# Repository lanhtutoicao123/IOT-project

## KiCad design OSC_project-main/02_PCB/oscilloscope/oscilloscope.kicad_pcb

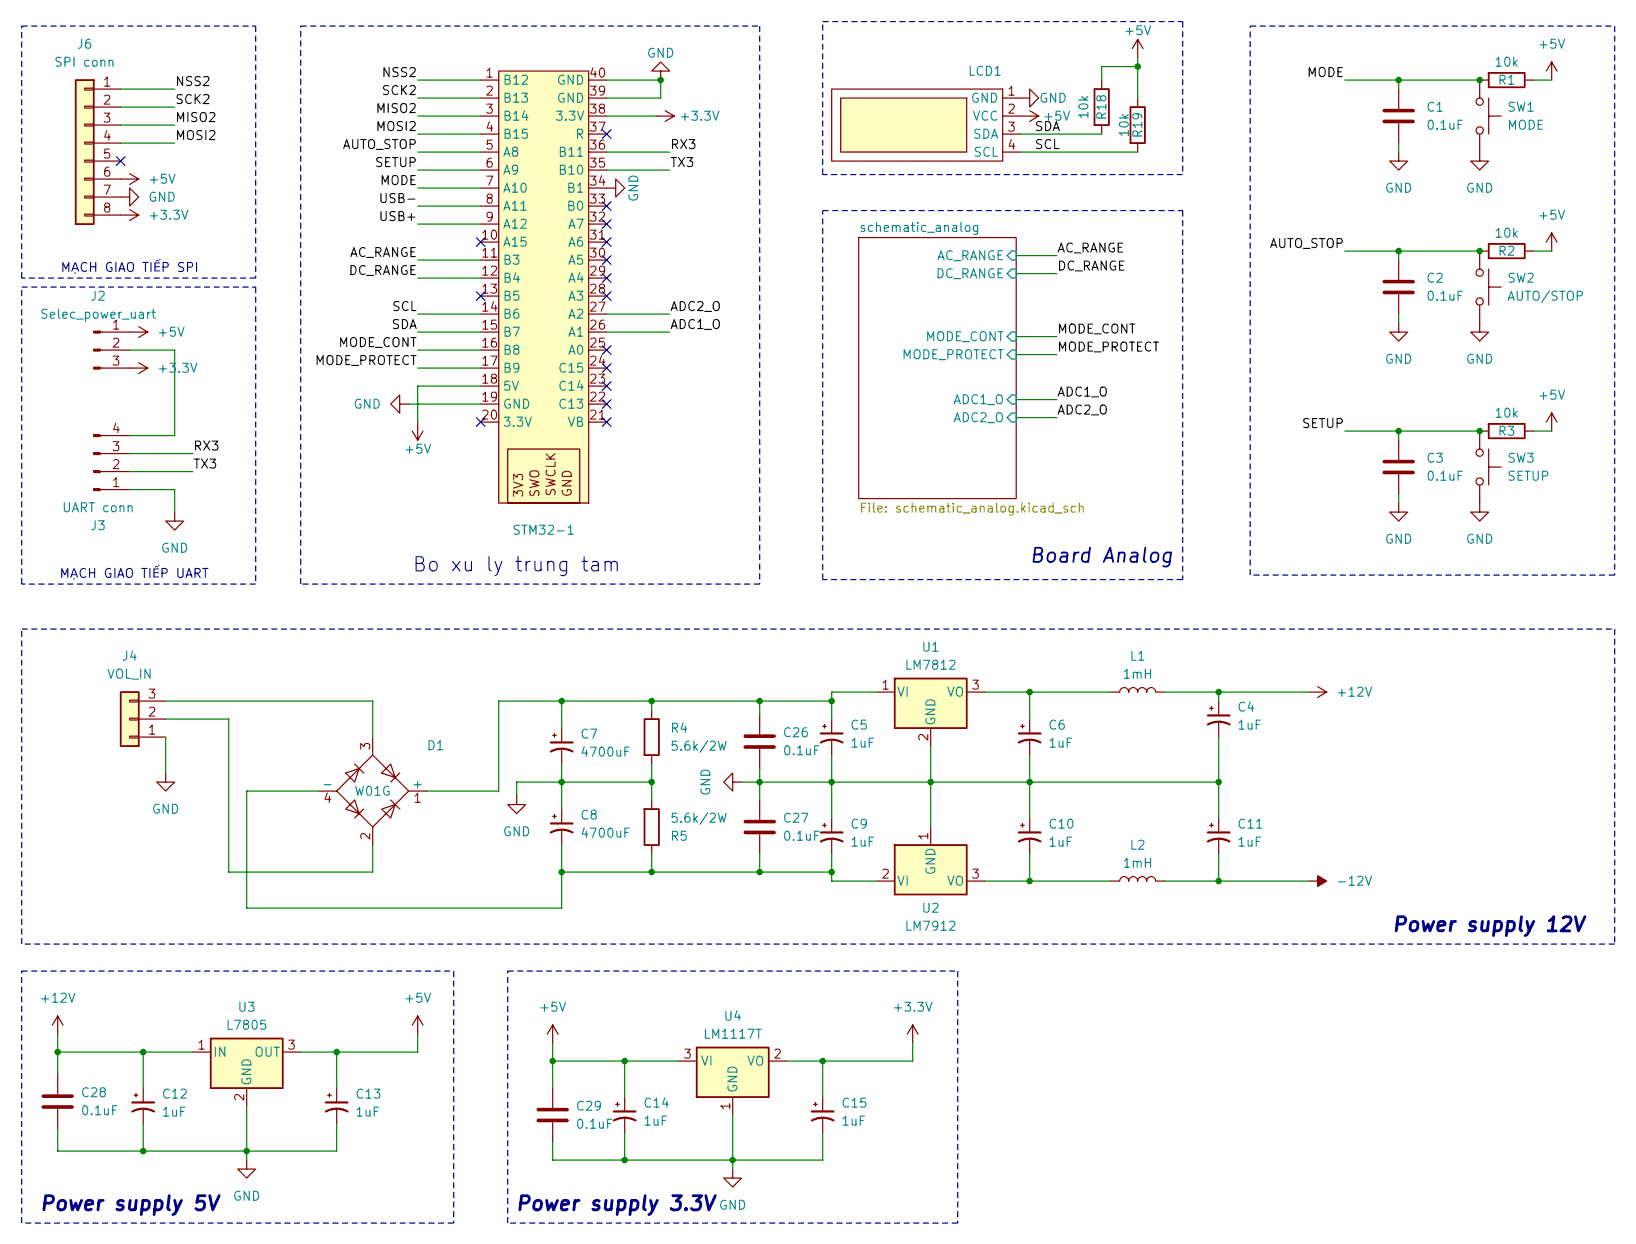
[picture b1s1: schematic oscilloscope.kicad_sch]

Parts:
C1, C2, C3: 0.1uF; C_Disc_D4.7mm_W2.5mm_P5.00mm
C4, C5, C6, C9, C10, C11, C12, C13, C14, C15: 1uF; CP_Radial_D6.3mm_P2.50mm
C7, C8: 4700uF; CP_Radial_D12.5mm_P5.00mm
C26, C27, C28, C29: 0.1uF; C_Disc_D4.3mm_W1.9mm_P5.00mm
D1: W01G; Diode_Bridge_Vishay_KBPM
J2: Selec_power_uart; PinHeader_1x03_P2.54mm_Vertical
J3: UART conn; PinHeader_1x04_P2.54mm_Vertical
J4: VOL_IN; PhoenixContact_MSTBA_2,5_3-G_1x03_P5.00mm_Horizontal
J6: SPI conn; PinHeader_1x08_P2.54mm_Vertical
L1, L2: 1mH; L_Axial_L7.0mm_D3.3mm_P10.16mm_Horizontal_Fastron_MICC
LCD1: LCD-I2C
R1, R18, R19: 10k; R_Axial_DIN0309_L9.0mm_D3.2mm_P12.70mm_Horizontal
R2, R3: 10k; R_Axial_DIN0207_L6.3mm_D2.5mm_P15.24mm_Horizontal
R4, R5: 5.6k/2W; R_Axial_DIN0516_L15.5mm_D5.0mm_P20.32mm_Horizontal
STM32-1: Kit_STM32F103C8T6
SW1: MODE; SW_PUSH-12mm
SW2: AUTO/STOP; SW_PUSH-12mm
SW3: SETUP; SW_PUSH-12mm
U1: LM7812; TO-220-3_Vertical
U2: LM7912; TO-220-3_Vertical
U3: L7805; TO-220-3_Vertical
U4: LM1117T; TO-220-3_Vertical

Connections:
+3.3V: C15.1, J2.3, J6.8, STM32-1.38 (3.3V), U4.2 (VO)
+5V: C13.1, C14.1, C29.2, J2.1, J6.6, LCD1.2 (VCC), R1.1, R2.1, R3.1, R18.1, R19.1, STM32-1.18 (5V), U3.3 (OUT), U4.3 (VI); also elsewhere on the board
+12V: C4.1, C12.1, C28.2, L1.2, U3.1 (IN); also elsewhere on the board
-12V: C11.2, L2.2; also elsewhere on the board
/AC_RANGE: STM32-1.11 (B3); also elsewhere on the board
/ADC1_O: STM32-1.26 (A1); also elsewhere on the board
/ADC2_O: STM32-1.27 (A2); also elsewhere on the board
/AUTO_STOP: C2.1, R2.2, STM32-1.5 (A8), SW2.2
/DC_RANGE: STM32-1.12 (B4); also elsewhere on the board
/MISO2: J6.3, STM32-1.3 (B14)
/MODE: C1.1, R1.2, STM32-1.7 (A10), SW1.2
/MODE_CONT: STM32-1.16 (B8); also elsewhere on the board
/MODE_PROTECT: STM32-1.17 (B9); also elsewhere on the board
/MOSI2: J6.4, STM32-1.4 (B15)
/NSS2: J6.1, STM32-1.1 (B12)
/RX3: J3.3, STM32-1.36 (B11)
/SCK2: J6.2, STM32-1.2 (B13)
/SCL: LCD1.4 (SCL), R19.2, STM32-1.14 (B6)
/SDA: LCD1.3 (SDA), R18.2, STM32-1.15 (B7)
/SETUP: C3.1, R3.2, STM32-1.6 (A9), SW3.2
/TX3: J3.2, STM32-1.35 (B10)
/USB+: STM32-1.9 (A12)
/USB-: STM32-1.8 (A11)
GND: C1.2, C2.2, C3.2, C4.2, C5.2, C6.2, C7.2, C8.1, C9.1, C10.1, C11.1, C12.2, C13.2, C14.2, C15.2, C26.1, C27.2, C28.1, C29.1, J3.1, J4.1, J6.7, LCD1.1 (GND), R4.2, R5.2, STM32-1.19 (GND), STM32-1.34 (B1), STM32-1.39 (GND), STM32-1.40 (GND), SW1.1, SW2.1, SW3.1, U1.2 (GND), U2.1 (GND), U3.2 (GND), U4.1 (GND); also elsewhere on the board
unnamed: C5.1, C7.1, C26.2, D1.1 (+), R4.1, U1.1 (VI)
unnamed: C8.2, C9.2, C27.1, D1.4 (-), R5.1, U2.2 (VI)
unnamed: J2.2, J3.4
unnamed: D1.2, J4.2
unnamed: D1.3, J4.3
unnamed: C6.1, L1.1, U1.3 (VO)
unnamed: C10.2, L2.1, U2.3 (VO)

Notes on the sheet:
Power supply 5V
MẠCH GIAO TIẾP SPI
Power supply 3.3V
Board Analog
Power supply 12V
MẠCH GIAO TIẾP UART
Bo xu ly trung tam

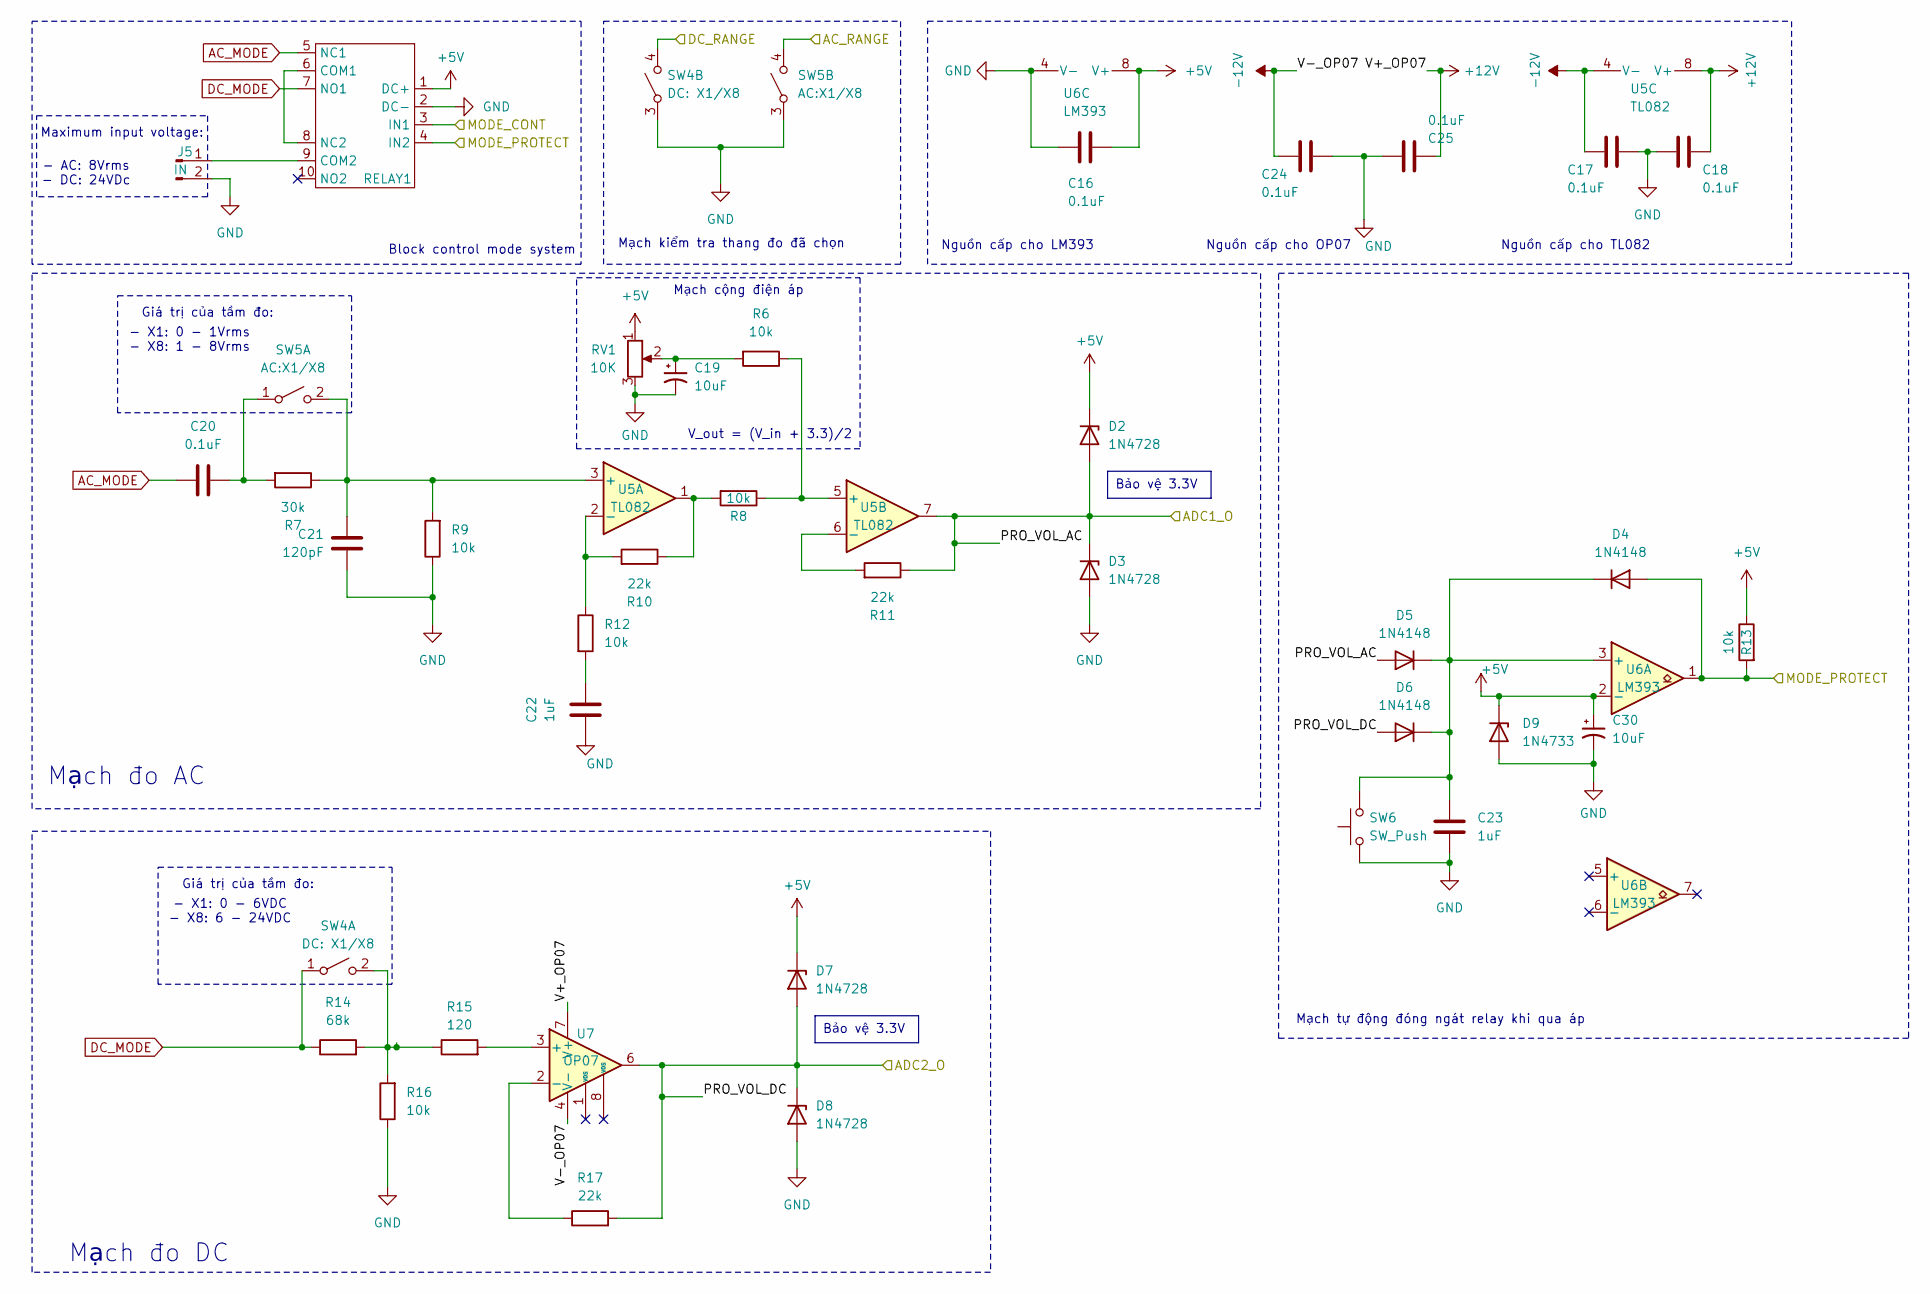
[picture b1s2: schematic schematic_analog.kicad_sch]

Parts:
C16, C17, C18, C20, C24, C25: 0.1uF; C_Disc_D4.3mm_W1.9mm_P5.00mm
C19: 10uF; CP_Radial_D4.0mm_P2.00mm
C21: 120pF; C_Disc_D4.3mm_W1.9mm_P5.00mm
C22, C23: 1uF; C_Disc_D4.3mm_W1.9mm_P5.00mm
C30: 10uF; CP_Radial_D6.3mm_P2.50mm
D2, D3, D7, D8: 1N4728; D_DO-34_SOD68_P7.62mm_Horizontal
D4, D5, D6: 1N4148; D_DO-34_SOD68_P7.62mm_Horizontal
D9: 1N4733; D_DO-34_SOD68_P7.62mm_Horizontal
J5: IN; Banana_Jack_2Pin
R6, R8, R9, R12, R16: 10k; R_Axial_DIN0207_L6.3mm_D2.5mm_P10.16mm_Horizontal
R7: 30k; R_Axial_DIN0207_L6.3mm_D2.5mm_P10.16mm_Horizontal
R10, R11, R17: 22k; R_Axial_DIN0207_L6.3mm_D2.5mm_P10.16mm_Horizontal
R13: 10k; R_Axial_DIN0207_L6.3mm_D2.5mm_P15.24mm_Horizontal
R14: 68k; R_Axial_DIN0207_L6.3mm_D2.5mm_P10.16mm_Horizontal
R15: 120; R_Axial_DIN0207_L6.3mm_D2.5mm_P15.24mm_Horizontal
RELAY1: Module_Relay5VDC
RV1: 10K; Potentiometer_Piher_PT-6-V_Vertical
SW4: DC: X1/X8; switch_02_3x2.5mm
SW5: AC:X1/X8; switch_02_3x2.5mm
SW6: SW_Push; SW_PUSH_1P1T_6x3.5mm_H4.3_APEM_MJTP1243
U5: TL082; DIP-8_W7.62mm_Socket
U6: LM393; DIP-8_W7.62mm_Socket
U7: OP07; DIP-8_W7.62mm_Socket

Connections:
+5V: C16.2, C30.1, D2.1 (K), D7.1 (K), D9.1 (K), R13.1, RELAY1.1 (DC+), RV1.1, U6.2 (-), U6.8 (V+); also elsewhere on the board
+12V: C18.2, C25.2, U5.8 (V+), U7.7 (V+); also elsewhere on the board
-12V: C17.1, C24.1, U5.4 (V-), U7.4 (V-); also elsewhere on the board
/AC_RANGE: SW5.4 (B); also elsewhere on the board
/ADC1_O: D2.2 (A), D3.1 (K), D5.2 (A), R11.1, U5.7; also elsewhere on the board
/ADC2_O: D6.2 (A), D7.2 (A), D8.1 (K), R17.2, U7.6; also elsewhere on the board
/DC_RANGE: SW4.4 (B); also elsewhere on the board
/MODE_CONT: RELAY1.3 (IN1); also elsewhere on the board
/MODE_PROTECT: D4.2 (A), R13.2, RELAY1.4 (IN2), U6.1; also elsewhere on the board
AC_MODE: C20.1, RELAY1.5 (NC1)
DC_MODE: R14.1, RELAY1.7 (NO1), SW4.1 (A)
GND: C16.1, C17.2, C18.1, C19.2, C21.1, C22.1, C23.2, C24.2, C25.1, C30.2, D3.2 (A), D8.2 (A), D9.2 (A), J5.2, R9.1, R16.1, RELAY1.2 (DC-), RV1.3, SW4.3 (A), SW5.3 (A), SW6.1, U6.4 (V-); also elsewhere on the board
unnamed: C19.1, R6.2, RV1.2
unnamed: C22.2, R12.2
unnamed: C23.1, D4.1 (K), D5.1 (K), D6.1 (K), SW6.2, U6.3 (+)
unnamed: J5.1, RELAY1.9 (COM2)
unnamed: R8.2, R10.1, U5.1
unnamed: RELAY1.6 (COM1), RELAY1.8 (NC2)
unnamed: R14.2, R15.1, R16.2, SW4.2 (B)
unnamed: C20.2, R7.2, SW5.1 (A)
unnamed: C21.2, R7.1, R9.2, SW5.2 (B), U5.3 (+)
unnamed: R10.2, R12.1, U5.2 (-)
unnamed: R6.1, R8.1, U5.5 (+)
unnamed: R11.2, U5.6 (-)
unnamed: R15.2, U7.3 (+)
unnamed: R17.1, U7.2 (-)

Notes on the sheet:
Bảo vệ 3.3V
Mạch cộng điện áp
Maximum input voltage:
- X1: 0 - 1Vrms - X8: 1 - 8Vrms
- AC: 8Vrms - DC: 24VDc
Mạch đo DC
V_out = (V_in + 3.3)/2
Mạch kiểm tra thang đo đã chọn
Nguồn cấp cho OP07
Mạch tự động đóng ngát relay khi qua áp
Nguồn cấp cho TL082
Block control mode system
Nguồn cấp cho LM393
Giá trị của tầm đo:
Mạch đo AC
- X1: 0 - 6VDC - X8: 6 - 24VDC

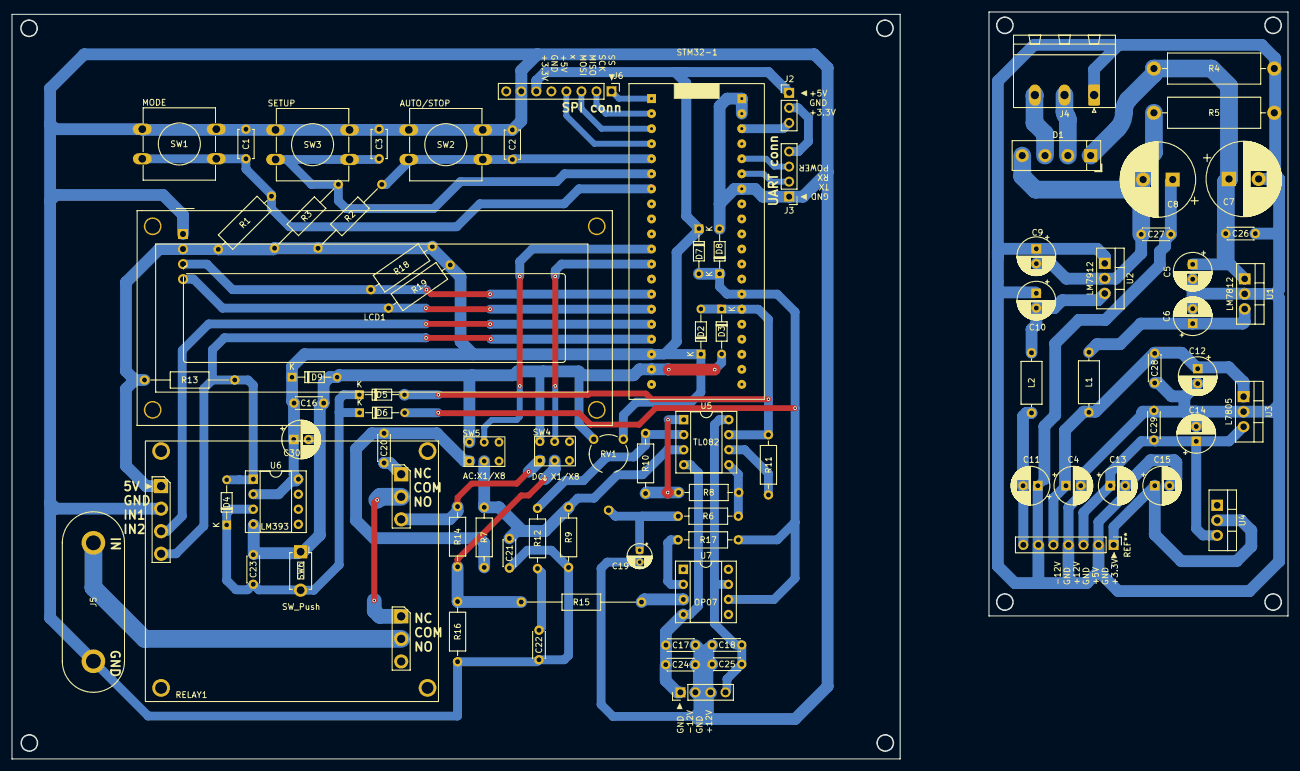
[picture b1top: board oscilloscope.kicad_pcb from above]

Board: 2 copper layers, 215.5 x 126.2 mm, 82 parts (0 on the bottom side), 45 nets.

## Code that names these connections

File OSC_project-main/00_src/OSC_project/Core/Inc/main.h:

/* USER CODE BEGIN Header */
/**
  ******************************************************************************
  * @file           : main.h
  * @brief          : Header for main.c file.
  *                   This file contains the common defines of the application.
  ******************************************************************************
  * @attention
  *
  * Copyright (c) 2024 STMicroelectronics.
  * All rights reserved.
  *
  * This software is licensed under terms that can be found in the LICENSE file
  * in the root directory of this software component.
  * If no LICENSE file comes with this software, it is provided AS-IS.
  *
  ******************************************************************************
  */
/* USER CODE END Header */

/* Define to prevent recursive inclusion -------------------------------------*/
#ifndef __MAIN_H
#define __MAIN_H

#ifdef __cplusplus
extern "C" {
#endif

/* Includes ------------------------------------------------------------------*/
#include "stm32f1xx_hal.h"

/* Private includes ----------------------------------------------------------*/
/* USER CODE BEGIN Includes */

/* USER CODE END Includes */

/* Exported types ------------------------------------------------------------*/
/* USER CODE BEGIN ET */

/* USER CODE END ET */

/* Exported constants --------------------------------------------------------*/
/* USER CODE BEGIN EC */

/* USER CODE END EC */

/* Exported macro ------------------------------------------------------------*/
/* USER CODE BEGIN EM */

/* USER CODE END EM */

/* Exported functions prototypes ---------------------------------------------*/
void Error_Handler(void);

/* USER CODE BEGIN EFP */

/* USER CODE END EFP */

/* Private defines -----------------------------------------------------------*/
#define START_Pin GPIO_PIN_8
#define START_GPIO_Port GPIOA
#define START_EXTI_IRQn EXTI9_5_IRQn
#define MODE_Pin GPIO_PIN_9
#define MODE_GPIO_Port GPIOA
#define MODE_EXTI_IRQn EXTI9_5_IRQn
#define SETUP_Pin GPIO_PIN_10
#define SETUP_GPIO_Port GPIOA
#define SETUP_EXTI_IRQn EXTI15_10_IRQn
#define AC_RANGE_Pin GPIO_PIN_3
#define AC_RANGE_GPIO_Port GPIOB
#define DC_RANGE_Pin GPIO_PIN_4
#define DC_RANGE_GPIO_Port GPIOB
#define MODE_CONT_Pin GPIO_PIN_8
#define MODE_CONT_GPIO_Port GPIOB
#define MODE_PRO_Pin GPIO_PIN_9

#define MODE_PRO_GPIO_Port  GPIOB
/* USER CODE BEGIN Private defines */

/* USER CODE END Private defines */

#ifdef __cplusplus
}
#endif

#endif /* __MAIN_H */

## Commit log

2025-02-15 first commit
    air project
2025-02-15 osc project
    2'rd commit
2025-02-15 3'rd
    Remove Some file
